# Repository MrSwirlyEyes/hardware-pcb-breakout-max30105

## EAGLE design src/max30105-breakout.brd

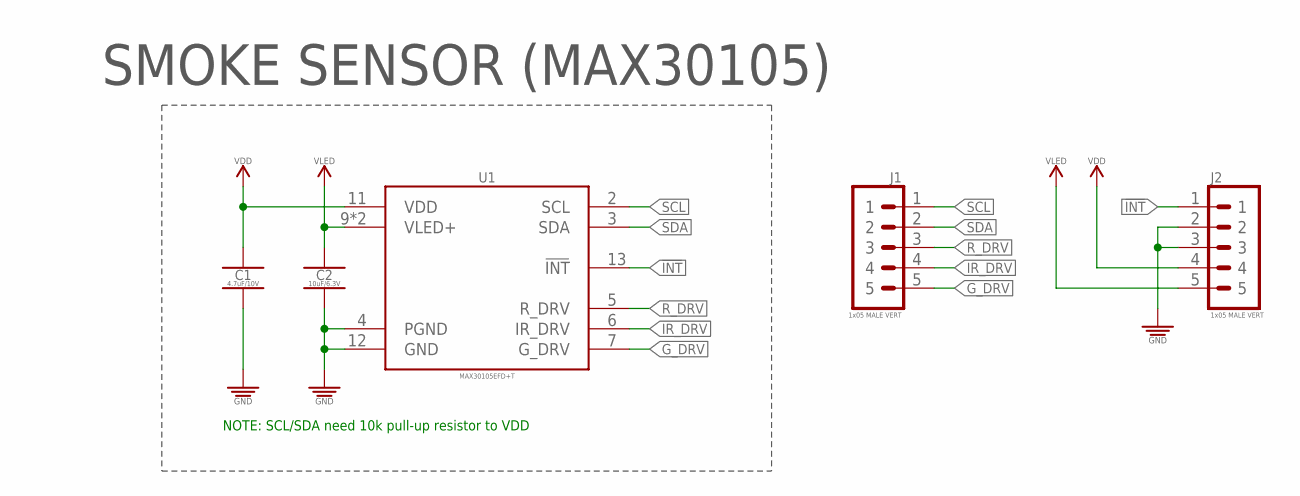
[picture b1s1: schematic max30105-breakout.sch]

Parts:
C1: 4.7uF/10V; CAPC1005X55_SMD-0402
C2: 10uF/6.3V; CAPC1005X55_SMD-0402
J1, J2: 1x05 MALE VERT; HDRV5W64P254_1X5_1270X254X838B
U1: MAX30105EFD+T; SON80P330X560X165-14N

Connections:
!INT!: J2.1, U1.13 (!INT!)
GND: C1.2, C2.2, J2.2, J2.3, U1.4 (PGND), U1.12 (GND)
G_DRV: J1.5, U1.7 (G_DRV)
IR_DRV: J1.4, U1.6 (IR_DRV)
R_DRV: J1.3, U1.5 (R_DRV)
SCL: J1.1, U1.2 (SCL)
SDA: J1.2, U1.3 (SDA)
VDD: C1.1, J2.4, U1.11 (VDD)
VLED: C2.1, J2.5, U1.9 (VLED+), U1.10 (VLED+)

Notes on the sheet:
SMOKE SENSOR (MAX30105)
NOTE: SCL/SDA need 10k pull-up resistor to VDD

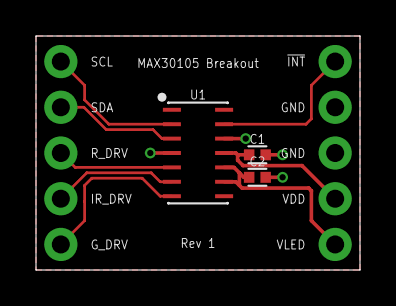
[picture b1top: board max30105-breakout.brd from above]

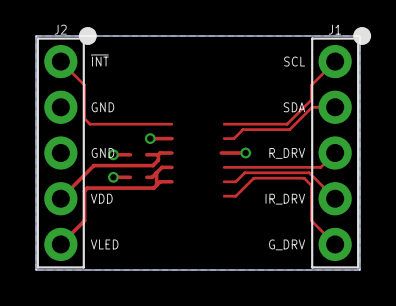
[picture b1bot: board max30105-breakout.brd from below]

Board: 2 copper layers, 18.0 x 13.0 mm, 5 parts (2 on the bottom side), 9 nets.

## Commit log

2021-01-12 [Rev 1] - Initialize repo.
2021-08-11 Update CAM files.
